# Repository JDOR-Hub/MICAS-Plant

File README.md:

# Measurement, Instrumentation, Control, and Automatization System for Plant's Health

## Description
MICAS is an IoT-based system for monitoring and automating irrigation and fertilization in agricultural or garden environments. It uses an ESP32 microcontroller to read multiple sensors (soil moisture, temperature, NPK nutrients, ambient light, humidity, temperature, water level) and control actuators (water pump, electrovalve). Data is published via MQTT to a Node-RED dashboard for visualization and alerts. The system is containerized using Docker for easy deployment of the MQTT broker and Node-RED.

## Features
- Real time monitoring of soil moisture, temperature, NPK nutrients, ambient light, ambient temperature, ambient humidity, and water tank level.
- Automatic irrigatio based on soil moisture tresholds.
- Automatic fertilization triggered when NPK levels fall below configurable tresholds.
- Environmental alerts for abnormal temperature, humidity, light, or low water level.
- Data loggign to an SD card in CSV format.
- MQTT integration for remote monitoring and control.
- Node-RED dashboard with live gauges, charts, and status LEDs.
- Dockerized infrastructure (Mosquitto + Node-RED) for easy setup.

## Hardware Components
1. ESP32 Dev Board
2. Soil Moisture Sensor (FC-28)
3. Soil Temperature Sensor (Thermistor)
4. NPK Sensor (RS485)
5. LDR (Light Sensor)
6. Water Level Sensor (Two wires)
7. DHT11 (Ambient Temp/Hum)
8. Water Pump Relay
9. Electrovalve Relay
10. SD Card Module (SPI)
11. MAX485 (RS485 to TTL)

## Schematic Diagrams
- [MICAS_SCH](Docs/MICAS_SCH.pdf)
- [Docs/MICAS_SCHEM](Docs/MICAS_SCHEM.pdf)
- [MICAS_PCB](Docs/MICAS_PCB.pdf)

## Software Components
* Arduino Code: Runs on ESP32, reads sensors, controls actuators, logs data to SD card, and publishes to MQTT.
* Mosquitto MQTT Borker: Handles message passing between ESPE32 and Node-RED
* Node-RED: Provides a visual dashboard and flow-based logic for data visualization and alerts.
* Docker Compose: Mosquitto and Node-RED containers

## MQTT Topics
The ESP32 publishes sensor readings and actuator states to the following topics (default):

* `esp32/SOILHUM` – Soil humidity (%)
* `esp32/SOILTEMP` – Soil temperature (°C)
* `esp32/SOILNUTN` – Nitrogen (mg/kg)
* `esp32/SOILNUTP` – Phosphorus (mg/kg)
* `esp32/SOILNUTK` – Potassium (mg/kg)
* `esp32/AMBHUM` – Ambient humidity (%)
* `esp32/AMBTEMP` – Ambient temperature (°C)
* `esp32/LDRVAL` – Light intensity (raw)
* `esp32/LVLVAL` – Water level (raw) – also used for low-water alert
* `esp32/WP1S` – Water pump 1 status (0/1)
* `esp32/WP2S` – Water pump 2 status (0/1)
* `esp32/EVS` – Electrovalve status (0/1)
* `esp32/Nutrientstatus` – Nutrient low alert (0/1)

## Other Information
- Authors & Contact: juandospinor@gmail.com

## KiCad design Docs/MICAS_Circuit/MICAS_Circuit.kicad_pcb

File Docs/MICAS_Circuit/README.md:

## MAIN FOLDER FOR KICAD SOFTWARE

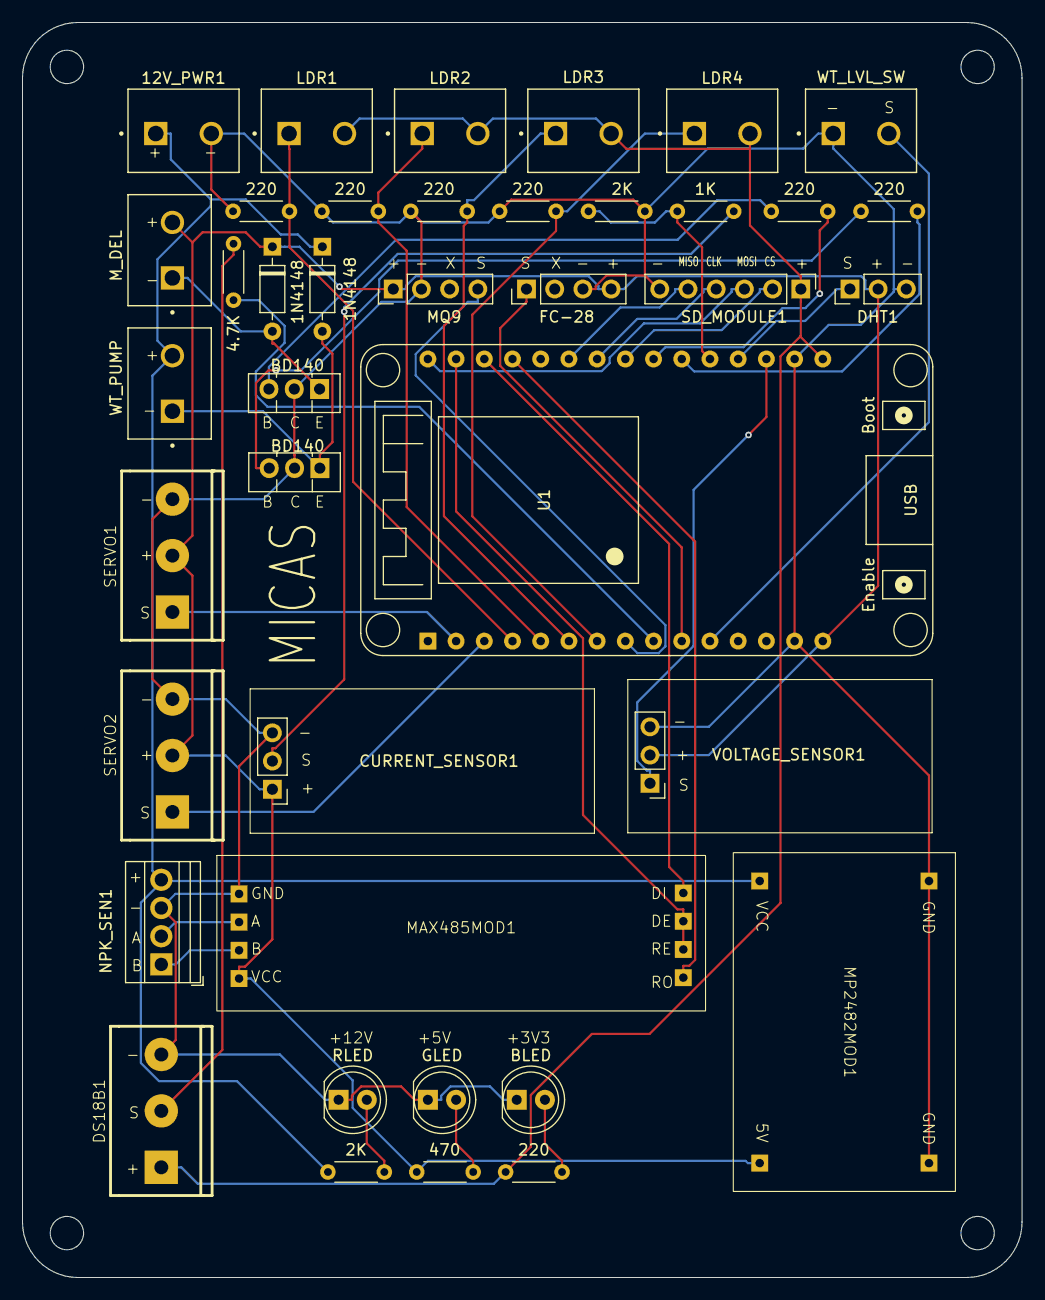
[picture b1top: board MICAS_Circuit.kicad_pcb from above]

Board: 2 copper layers, 90.0 x 113.0 mm, 40 parts (0 on the bottom side), 37 nets.

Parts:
12V_PWR1: Screw_Terminal_01x02; KF301-2P
CURRENT_SENSOR1: DHT11; PinHeader_1x03_P2.54mm_Vertical
D1, D2: 1N4148; D_DO-35_SOD27_P7.62mm_Horizontal
D3: RLED; LED_D5.0mm_FlatTop
D4: GLED; LED_D5.0mm_FlatTop
D5: BLED; LED_D5.0mm_FlatTop
DHT1: DHT11; PinHeader_1x03_P2.54mm_Vertical
DS18B1: Screw_Terminal_01x03; KF301-3P
FC-28: FC-28-MOD; PinHeader_1x04_P2.54mm_Vertical
LDR1, LDR2, LDR3, LDR4: Screw_Terminal_01x02; KF301-2P
MAX485MOD1: MAX485_MOD
MP2482MOD1: MP2482_MOD
MQ9: FC-28-MOD; PinHeader_1x04_P2.54mm_Vertical
M_DEL: Screw_Terminal_01x02; KF301-2P
NPK_SEN1: Screw_Terminal_01x04; TerminalBlock_Xinya_XY308-2.54-4P_1x04_P2.54mm_Horizontal
Q1, Q2: BD140; TO-126-3_Vertical
R1, R2, R3, R4, R8, R9, R12: 220; R_Axial_DIN0204_L3.6mm_D1.6mm_P5.08mm_Horizontal
R5: 4.7K; R_Axial_DIN0204_L3.6mm_D1.6mm_P5.08mm_Horizontal
R6: 1K; R_Axial_DIN0204_L3.6mm_D1.6mm_P5.08mm_Horizontal
R7, R10: 2K; R_Axial_DIN0204_L3.6mm_D1.6mm_P5.08mm_Horizontal
R11: 470; R_Axial_DIN0204_L3.6mm_D1.6mm_P5.08mm_Horizontal
SD_MODULE1: Conn_01x06_Pin; PinHeader_1x06_P2.54mm_Vertical
SERVO1, SERVO2: Screw_Terminal_01x03; KF301-3P
U1: ESP32_DevKit_V1_DOIT; esp32_devkit_v1_doit
VOLTAGE_SENSOR1: DHT11; PinHeader_1x03_P2.54mm_Vertical
WT_LVL_SW: Screw_Terminal_01x02; KF301-2P
WT_PUMP: Screw_Terminal_01x02; KF301-2P

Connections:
+3V3: DS18B1.1, LDR1.2, LDR2.2, LDR3.2, LDR4.2, R12.1, SD_MODULE1.1, U1.16 (3V3)
+5V: CURRENT_SENSOR1.1, D1.1 (K), DHT1.2, FC-28.4, MAX485MOD1.4 (VCC), MP2482MOD1.3 (5V), MQ9.1, M_DEL.2, R11.1, SERVO1.2, SERVO2.2, U1.15 (VIN), VOLTAGE_SENSOR1.2
+12V: 12V_PWR1.1, D2.1 (K), MP2482MOD1.2 (VCC), NPK_SEN1.4, R10.1, WT_PUMP.2
A: MAX485MOD1.2 (A), NPK_SEN1.2
B: MAX485MOD1.3 (B), NPK_SEN1.1
CLK: SD_MODULE1.4, U1.24 (IO18)
CS: SD_MODULE1.2, U1.23 (IO5)
CURRSEN_SIGNAL: R6.2, R7.2, U1.20 (IO4)
DC_MOTOR_SIGNAL: R8.2, U1.22 (IO17)
DHT11_SIGNAL: DHT1.1, U1.19 (IO2)
DI_SIGNAL: MAX485MOD1.8 (DI), U1.28 (TXD0/IO1)
DS18B20_SIGNAL: R5.1, U1.9 (IO26)
FC28_SIGNAL: FC-28.1, U1.10 (IO27)
GND: 12V_PWR1.2, CURRENT_SENSOR1.3, D3.1 (K), D4.1 (K), D5.1 (K), DHT1.3, DS18B1.3, FC-28.3, MAX485MOD1.1 (GND), MP2482MOD1.1 (GND), MP2482MOD1.4 (GND), MQ9.2, NPK_SEN1.3, Q1.2 (C), Q2.2 (C), R1.1, R2.1, R3.1, R4.1, R7.1, SD_MODULE1.6, SERVO1.3, SERVO2.3, U1.14 (GND), U1.17 (GND), VOLTAGE_SENSOR1.3, WT_LVL_SW.1
LDR1_SIGNAL: LDR1.1, R1.2, U1.4 (IO34)
LDR2_SIGNAL: LDR2.1, R2.2, U1.5 (IO35)
LDR3_SIGNAL: LDR3.1, R3.2, U1.6 (IO32)
LDR4_SIGNAL: LDR4.1, R4.2, U1.7 (IO33)
MISO: SD_MODULE1.5, U1.25 (IO19)
MOSI: SD_MODULE1.3, U1.30 (IO23)
MQ9_SIGNAL: MQ9.4, U1.8 (IO25)
unnamed: CURRENT_SENSOR1.2, R6.1
unnamed: D1.2 (A), M_DEL.1, Q1.1 (E)
unnamed: D2.2 (A), Q2.1 (E), WT_PUMP.1
unnamed: D3.2 (A), R10.2
unnamed: D4.2 (A), R11.2
unnamed: D5.2 (A), R12.2
unnamed: DS18B1.2, R5.2
unnamed: Q1.3 (B), R8.1
unnamed: Q2.3 (B), R9.1
RE_SIGNAL: MAX485MOD1.6 (RE), MAX485MOD1.7 (DE), U1.29 (IO22)
RO_SIGNAL: MAX485MOD1.5 (RO), U1.27 (RXD0/IO3)
SERVO1_SIGNAL: SERVO1.1, U1.2 (SENSOR_VP)
SERVO2_SIGNAL: SERVO2.1, U1.3 (SENSOR_VN)
VOLTSEN_SIGNAL: U1.18 (IO15), VOLTAGE_SENSOR1.1
WATER_LEVEL_SIGNAL: U1.11 (IO14), WT_LVL_SW.2
WATER_PUMP_SIGNAL: R9.2, U1.21 (IO16)

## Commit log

2024-10-21 Create MICAS for Plant's Health repo
2024-10-21 update repository with circuit data
2024-10-21 edit main README file
2024-10-21 updates on the to-do list
2024-10-21 updates on the to do list file
2024-10-21 Check list of done items in to-do list
2024-10-21 Update list of done items in to-do list
2024-10-23 Add Schematic and PCB planes.
2024-10-23 Update 3D circuit
2024-12-03 Create .gitignore
    The file gitignore is create
2024-12-03 Create mosquitto.conf
    the mosquitto.conf file is created
2024-12-03 Rename node-red/data/.gitignore to node-red/data/.npm/.gitkeep
2024-12-03 The service from node-red is started
2024-12-03 The flow chart with humidity was created
2024-12-03 Update latest version of the project.
2024-12-03 Delete Docs/BOM_SmartGarden.xlsx
    Not necessary.
2024-12-03 Latest version of the code
2024-12-04 Add elements to the flowchart
2024-12-04 The 3 flow chart was create
2024-12-05 data simulate with ESP32
2026-03-14 update micas readme project file
2026-03-14 Fix link formatting for MICAS_SCH.pdf in README
2026-03-14 remove unused files
